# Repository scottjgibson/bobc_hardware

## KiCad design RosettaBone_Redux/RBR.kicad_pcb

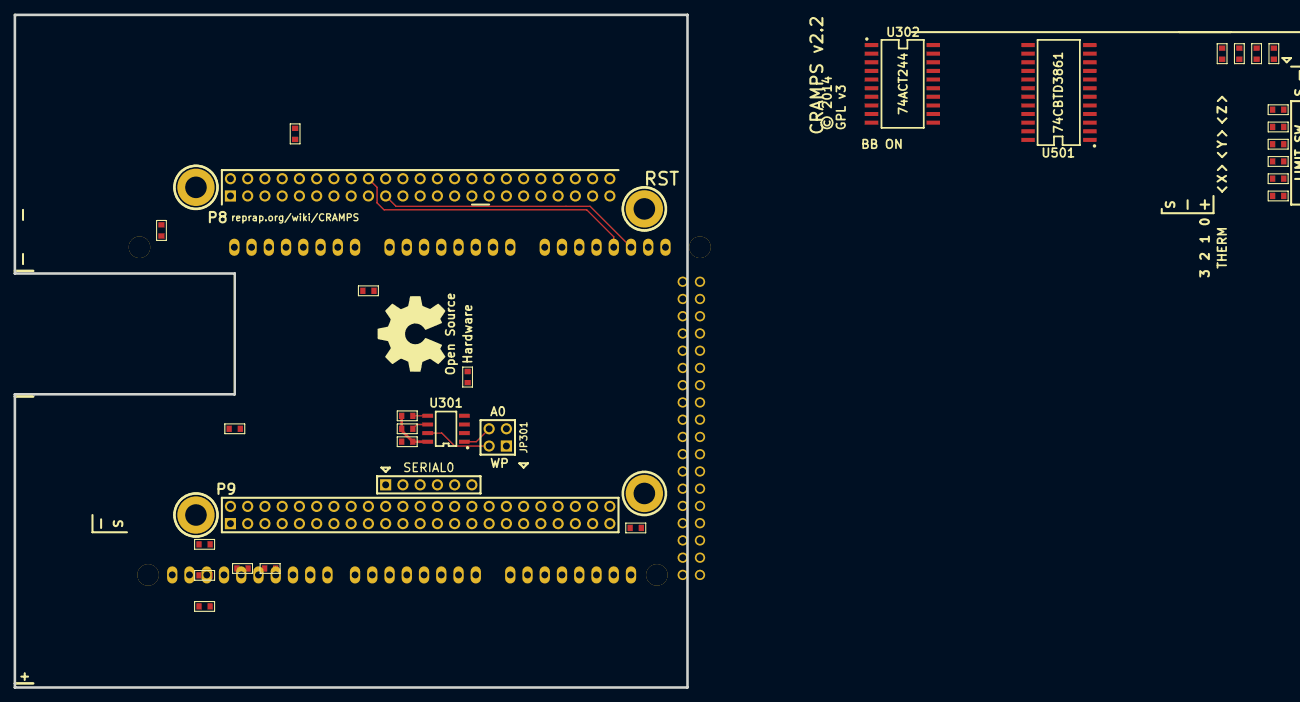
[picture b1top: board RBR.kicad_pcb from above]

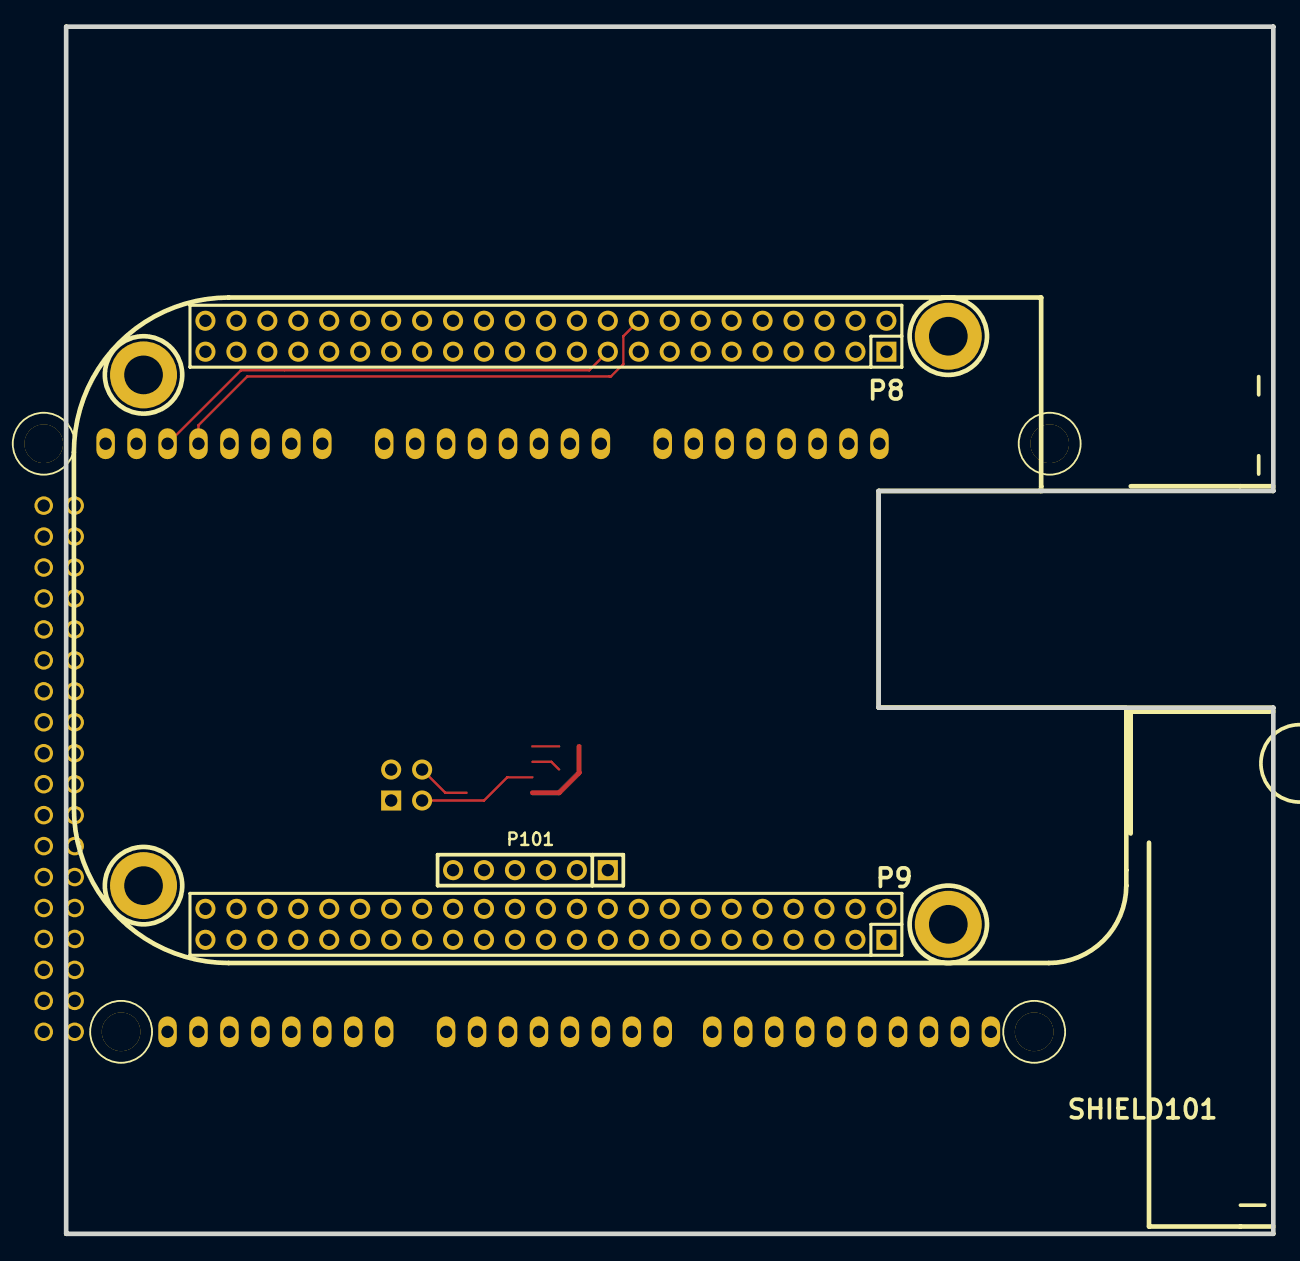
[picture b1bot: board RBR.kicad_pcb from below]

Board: 2 copper layers, 99.1 x 99.1 mm, 35 parts (5 on the bottom side), 61 nets.

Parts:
BB101: BeagleBone Black; BeagleBone-Pins
C301, C302, C501: 100n; CAPC1608x55N
JP301: HEADER_2X2; pin_strip_2x2
M101: PCB_GREEN_RMC; OSHW_logo_2
M102: LOGO_OSHW; PCB_GREEN_RMC
P8, P9: BB_EXP_CONN; P8P9_PinHeader
P101: SOCKET_6_LONG; pin_strip_6
R306, R307, R314: 4k7; RESC1608x55N
R308, R309, R310, R311, R312, R313, R315, R316, R501, R502, R503, R504, R505, R506, R507, R508, R509, R510: 10k; RESC1608x55N
SHIELD101: ARDUINO_DUE_SHIELD; ARDUINO_MEGA_DUE_SHIELD_FOOTPRINT_RMC
U301: 24C256; SOIC127P600X175-8AN
U302: 74ACT244; SOIC127P1032X265-20N
U501: 74CBTD3861; SOIC127P1030X265-24N

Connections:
/Inputs/MISO-5V: R507.2, U501.8
/Inputs/MOSI-5V: R509.2, U501.10
/Inputs/SCK-5V: R508.2, U501.9
/Inputs/SPI_CS0-5V: R510.2, U501.11
AXIS_ENAn: P9.14, U302.2, U302.4
D3.3V: C301.1, JP301.1, JP301.3, P9.3, P9.4, R306.1, R307.1, R310.1, R314.1, SHIELD101.3V3, U301.3, U301.8
D32: P9.24, SHIELD101.32
D41: P9.18, SHIELD101.41
D43: P9.17, SHIELD101.43
D47: P9.26, SHIELD101.47
DGND: BB101.M1, BB101.M2, BB101.M3, BB101.M4, C301.2, C302.2, C501.2, P8.1, P8.2, P9.1, P9.2, P9.43, P9.44, P9.45, P9.46, P101.1, R309.2, R311.2, R312.2, R313.2, R315.2, R316.2, SHIELD101.GND, U301.4, U302.10, U501.12, U501.23
E0_DIR: P9.12, SHIELD101.28
E0_EN_BUFn: R314.2, U302.18
E0_STEP: P9.16, SHIELD101.36
EN_CRAMP3n: R310.2, U302.16
ESTOP: P8.17, SHIELD101.40
FET1: P8.11, U302.17
FET1_BUF: R309.1, U302.3
FET2: P9.15, U302.15
FET2_BUF: R311.1, U302.5
FET3: P9.27, U302.13
FET3_BUF: R312.1, U302.7
FET4: P9.21, U302.11
FET4_BUF: R313.1, U302.9
FET5: P9.41, U302.6
FET5_BUF: R316.1, U302.14
FET6: P9.22, U302.8
FET6_BUF: R315.1, U302.12
GNDA: SHIELD101.GND4, SHIELD101.GND5
MISO: P9.29, U501.16
MOSI: P9.30, U501.14
unnamed: R506.2, U501.7
unnamed: R505.2, U501.6
unnamed: R504.2, U501.5
unnamed: R503.2, U501.4
unnamed: R502.2, U501.3
unnamed: R501.2, U501.2
unnamed: JP301.2, U301.7
unnamed: JP301.4, U301.1
SCK: P9.31, U501.15
SCL: P9.19, R306.2, SHIELD101.21, U301.6
SDA: P9.20, R307.2, SHIELD101.20, U301.5
SPI_CS0: P9.28, U501.13
SPI_CS1: P9.42, SHIELD101.4
SYS_5V: C302.1, C501.1, P9.7, P9.8, R308.1, R501.1, R502.1, R503.1, R504.1, R505.1, R506.1, R507.1, R508.1, R509.1, R510.1, U302.20, U501.24
THERM0: P9.33, SHIELD101.AD0
THERM1: P9.36, SHIELD101.AD1
THERM2: P9.35, SHIELD101.AD2
VDD_5V: P9.5, P9.6
X-MAX: P8.7, SHIELD101.30, U501.21
X-MIN: P8.8, SHIELD101.22, U501.22
X_DIR: P8.12, SHIELD101.AD8
X_STEP: P8.13, SHIELD101.AD9
Y-MAX: P8.9, SHIELD101.38, U501.19
Y-MIN: P8.10, SHIELD101.24, U501.20
Y_DIR: P8.14, SHIELD101.AD10
Y_STEP: P8.15, SHIELD101.AD11
Z-MAX: P9.11, SHIELD101.34, U501.17
Z-MIN: P9.13, SHIELD101.26, U501.18
Z_DIR: P8.18, SHIELD101.AD12
Z_STEP: P8.19, SHIELD101.AD13

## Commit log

2014-02-16 Redeuce size of PCB to 3.9" x 3.9" by just chopping off 0.050" from the top and bottom to test low-cost prototypes from iteadstudio.com (10x10 cm size limit)
2014-02-16 Added zip file sent to iteadstudio.com
2015-01-09 Initial Commit of RosettaBone Redux design
2015-01-14 Cleanup

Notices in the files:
RosettaBone_Redux/RBR.kicad_pcb:
Copyright 2014 GPL v3
© 2014
GPL v3
